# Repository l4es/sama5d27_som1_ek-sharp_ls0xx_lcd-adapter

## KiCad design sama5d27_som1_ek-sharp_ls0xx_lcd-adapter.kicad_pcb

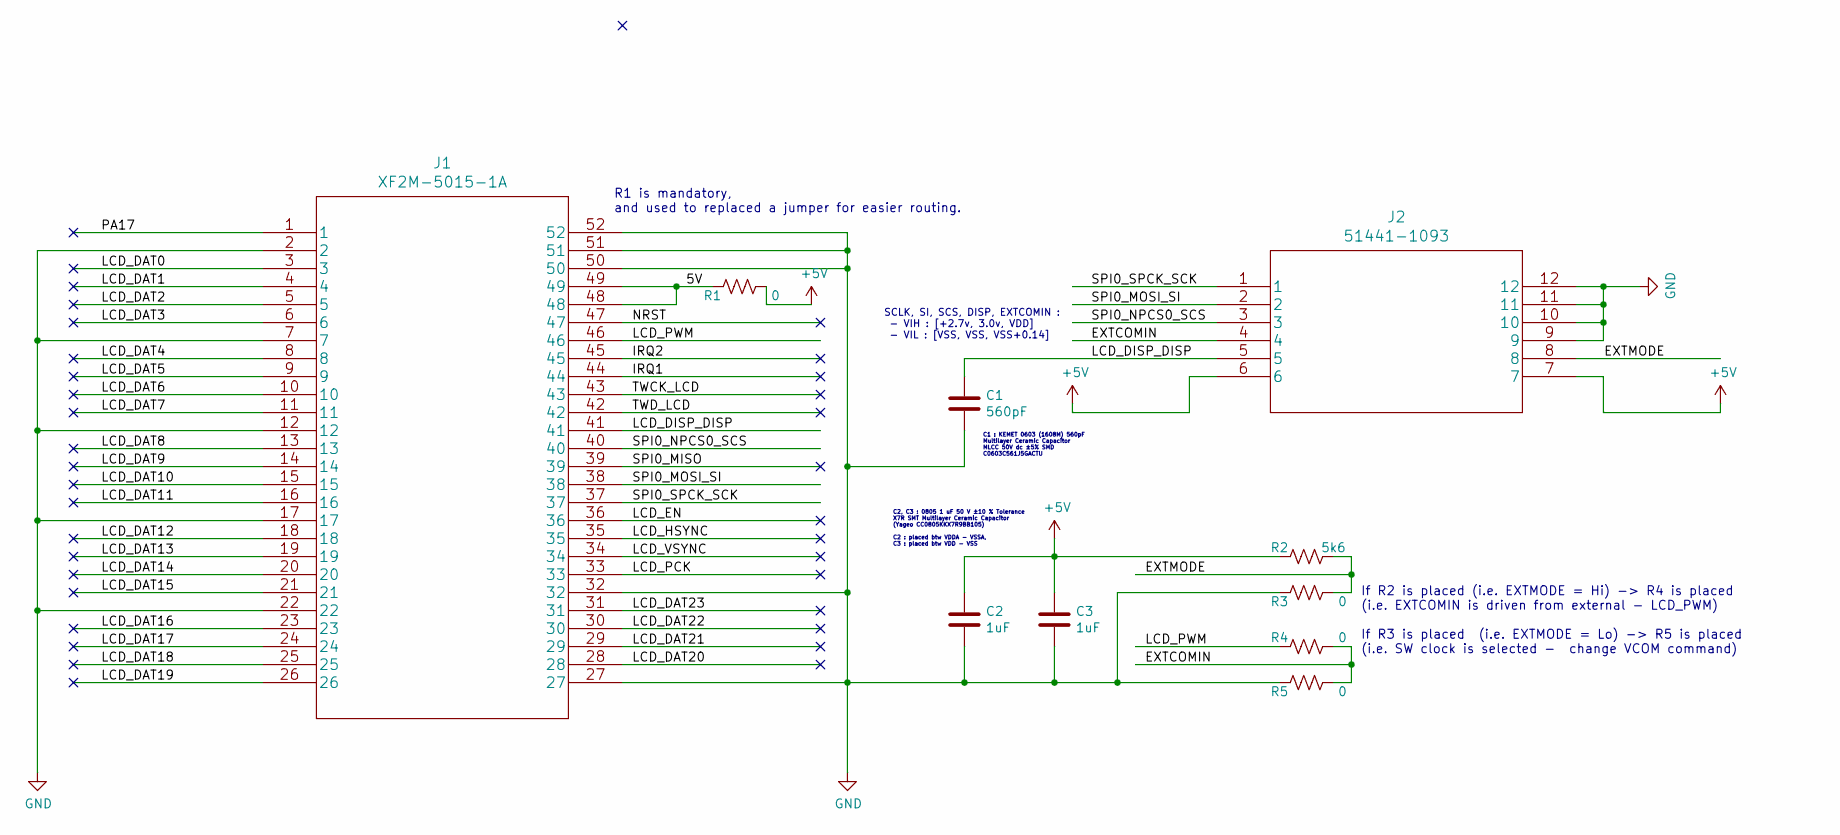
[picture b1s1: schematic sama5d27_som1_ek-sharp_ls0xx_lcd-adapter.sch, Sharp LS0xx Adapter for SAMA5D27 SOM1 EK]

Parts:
C1: 560pF; C_0603_1608Metric
C2, C3: 1uF; C_0805_2012Metric
J1: XF2M-5015-1A
J2: 51441-1093
R1, R3, R4, R5: 0; R_0805_2012Metric
R2: 5k6; R_0805_2012Metric

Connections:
+5V: C2.1, C3.1, J2.6, J2.7, R1.1, R2.2
/5V: J1.48, J1.49, R1.2
/EXTCOMIN: J2.4, R4.1, R5.1
/EXTMODE: J2.8, R2.1, R3.1
/IRQ1: J1.44
/IRQ2: J1.45
/LCD_DAT0: J1.3
/LCD_DAT1: J1.4
/LCD_DAT2: J1.5
/LCD_DAT3: J1.6
/LCD_DAT4: J1.8
/LCD_DAT5: J1.9
/LCD_DAT6: J1.10
/LCD_DAT7: J1.11
/LCD_DAT8: J1.13
/LCD_DAT9: J1.14
/LCD_DAT10: J1.15
/LCD_DAT11: J1.16
/LCD_DAT12: J1.18
/LCD_DAT13: J1.19
/LCD_DAT14: J1.20
/LCD_DAT15: J1.21
/LCD_DAT16: J1.23
/LCD_DAT17: J1.24
/LCD_DAT18: J1.25
/LCD_DAT19: J1.26
/LCD_DAT20: J1.28
/LCD_DAT21: J1.29
/LCD_DAT22: J1.30
/LCD_DAT23: J1.31
/LCD_DISP_DISP: C1.1, J1.41, J2.5
/LCD_EN: J1.36
/LCD_HSYNC: J1.35
/LCD_PCK: J1.33
/LCD_PWM: J1.46, R4.2
/LCD_VSYNC: J1.34
/NRST: J1.47
/PA17: J1.1
/SPI0_MISO: J1.39
/SPI0_MOSI_SI: J1.38, J2.2
/SPI0_NPCS0_SCS: J1.40, J2.3
/SPI0_SPCK_SCK: J1.37, J2.1
/TWCK_LCD: J1.43
/TWD_LCD: J1.42
GND: C1.2, C2.2, C3.2, J1.2, J1.7, J1.12, J1.17, J1.22, J1.27, J1.32, J1.50, J1.51, J1.52, J2.9, J2.10, J2.11, J2.12, R3.2, R5.2

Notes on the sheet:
C2, C3 : 0805 1 uF 50 V ±10 % Tolerance X7R SMT Multilayer Ceramic Capacitor (Yageo CC0805KKX7R9BB105) C2 : placed btw VDDA - VSSA, C3 : placed btw VDD - VSS
R1 is mandatory, and used to replaced a jumper for easier routing.
If R2 is placed (i.e. EXTMODE = Hi) -> R4 is placed (i.e. EXTCOMIN is driven from external - LCD_PWM) If R3 is placed (i.e. EXTMODE = Lo) -> R5 is placed (i.e. SW clock is selected - change VCOM command)
SCLK, SI, SCS, DISP, EXTCOMIN : - VIH : [+2.7v, 3.0v, VDD] - VIL : [VSS, VSS, VSS+0.14]
C1 : KEMET 0603 (1608M) 560pF Multilayer Ceramic Capacitor MLCC 50V dc ±5% SMD C0603C561J5GACTU

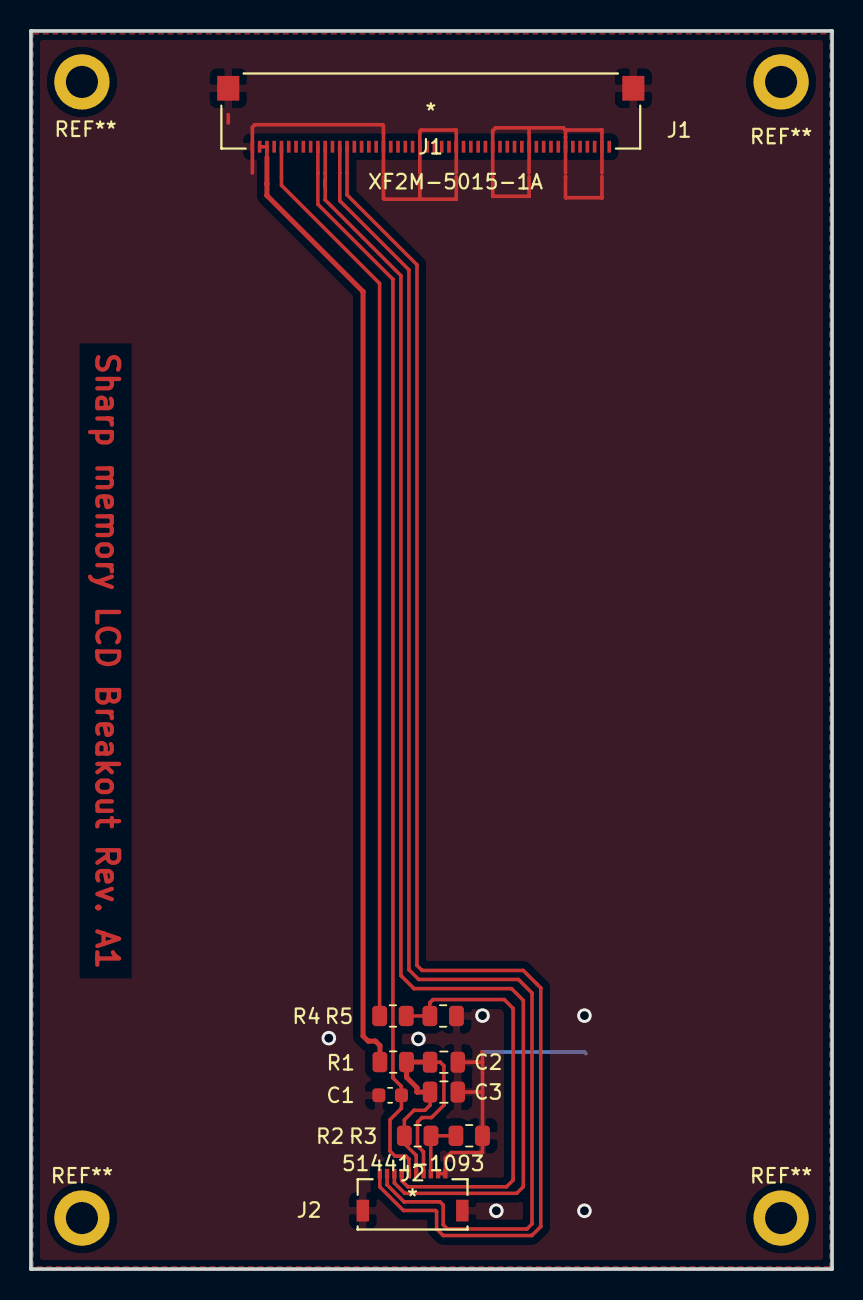
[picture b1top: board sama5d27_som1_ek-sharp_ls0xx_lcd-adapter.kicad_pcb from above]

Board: 2 copper layers, 55.0 x 85.0 mm, 10 parts (0 on the bottom side), 10 nets.

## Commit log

2020-11-09 Updaload revision A0
2020-11-09 Add missing symbol libraries
2020-11-10 Pump to revision A1 (replacing J2)
2020-11-12 Update RevA1
2020-11-12 Centralize pcb in sheet
2020-11-12 Update revision text on board
